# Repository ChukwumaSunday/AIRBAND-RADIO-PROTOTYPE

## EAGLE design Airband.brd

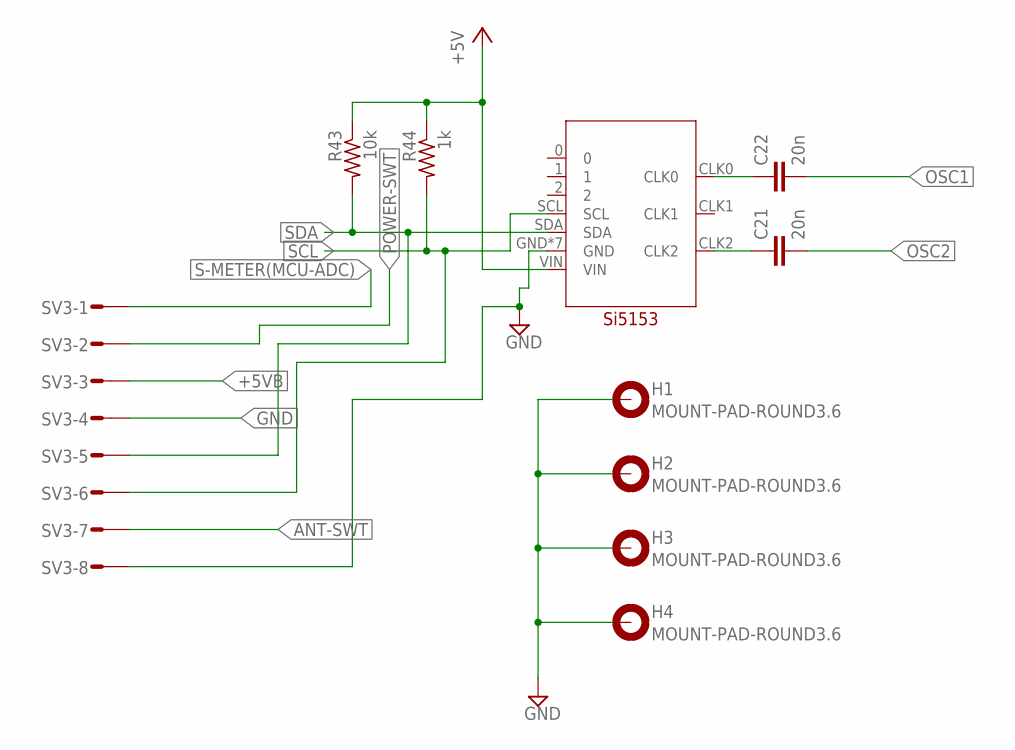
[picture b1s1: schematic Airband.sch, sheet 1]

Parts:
C21, C22: 20n; C0805
H1, H2, H3, H4: MOUNT-PAD-ROUND3.6; 3,6-PAD
R43: 10k; R0805
R44: 1k; R0805
SV3: MT6-8
U$10: DEVELOPMENT-BOARDS$1_SI5153SI5153; DEVELOPMENT-BOARDS$1_SI5153

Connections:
+5VA: R43.1, R44.1, U$10.VIN; also elsewhere on the board
+5VB: SV3.3; also elsewhere on the board
ANT-SWT: SV3.7; also elsewhere on the board
GND: H1.B3,6, H2.B3,6, H3.B3,6, H4.B3,6, SV3.4, SV3.8, U$10.GND, U$10.GND0 (GND), U$10.GND00 (GND), U$10.GND1 (GND), U$10.GND2 (GND), U$10.GND11 (GND), U$10.GND22 (GND); also elsewhere on the board
unnamed: C21.1, U$10.CLK2
unnamed: C22.1, U$10.CLK0
OSC1: C22.2; also elsewhere on the board
OSC2: C21.2; also elsewhere on the board
POWER-SWT: SV3.2; also elsewhere on the board
S-METER(MCU-ADC): SV3.1; also elsewhere on the board
SCL: R44.2, SV3.6, U$10.SCL
SDA: R43.2, SV3.5, U$10.SDA

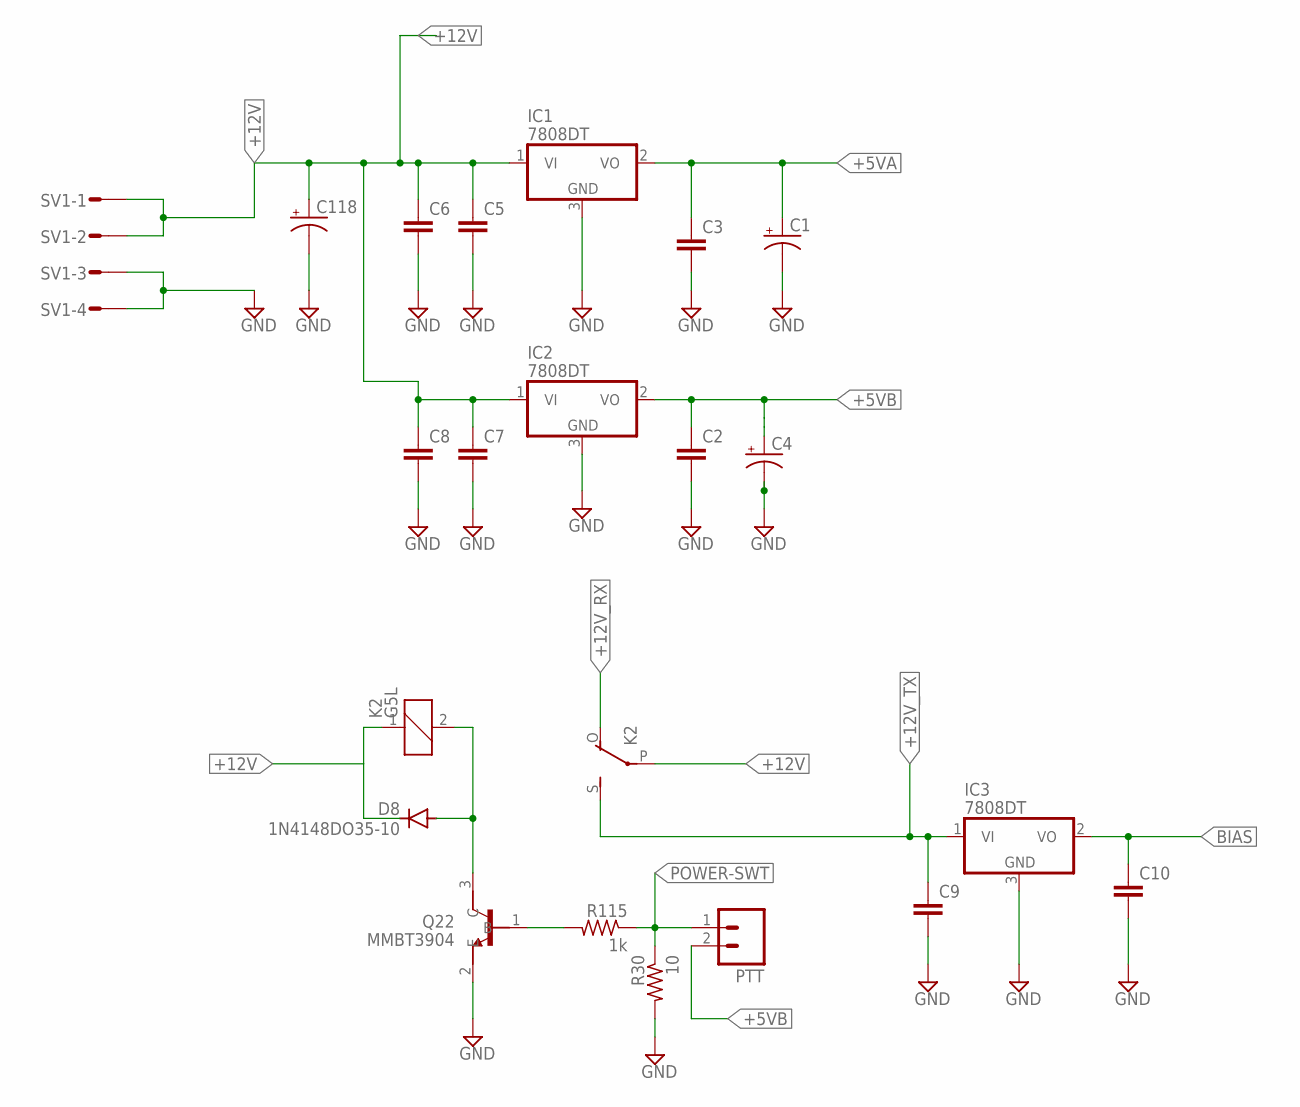
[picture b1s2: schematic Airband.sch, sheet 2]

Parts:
C1, C4, C118: CPOL-US153CLV-0405; 153CLV-0405
C2, C3, C5, C6, C7, C8, C9, C10: C-EUC0805; C0805
D8: 1N4148DO35-10; DO35-7SMD
IC1, IC2, IC3: 7808DT; TO252
K2: G5L; G5LE
PTT: M02; 02P
Q22: MMBT3904; SOT95P240X120-3N
R30: 10; R0805
R115: 1k; R0805
SV1: MT6-4Y

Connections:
+5VA: C1.+, C3.1, IC1.2 (VO); also elsewhere on the board
+5VB: C2.1, C4.+, IC2.2 (VO), PTT.2; also elsewhere on the board
+12V: C5.1, C6.1, C7.1, C8.1, C118.+, D8.C, IC1.1 (VI), IC2.1 (VI), K2.1, K2.P, SV1.1, SV1.2; also elsewhere on the board
+12V_RX: K2.O
+12V_TX: C9.1, IC3.1 (VI), K2.S
BIAS: C10.1, IC3.2 (VO); also elsewhere on the board
GND: C1.-, C2.2, C3.2, C4.-, C5.2, C6.2, C7.2, C8.2, C9.2, C10.2, C118.-, IC1.3 (GND), IC2.3 (GND), IC3.3 (GND), Q22.2 (E), R30.2, SV1.3, SV1.4; also elsewhere on the board
unnamed: D8.A, K2.2, Q22.3 (C)
unnamed: Q22.1 (B), R115.2
POWER-SWT: PTT.1, R30.1, R115.1; also elsewhere on the board

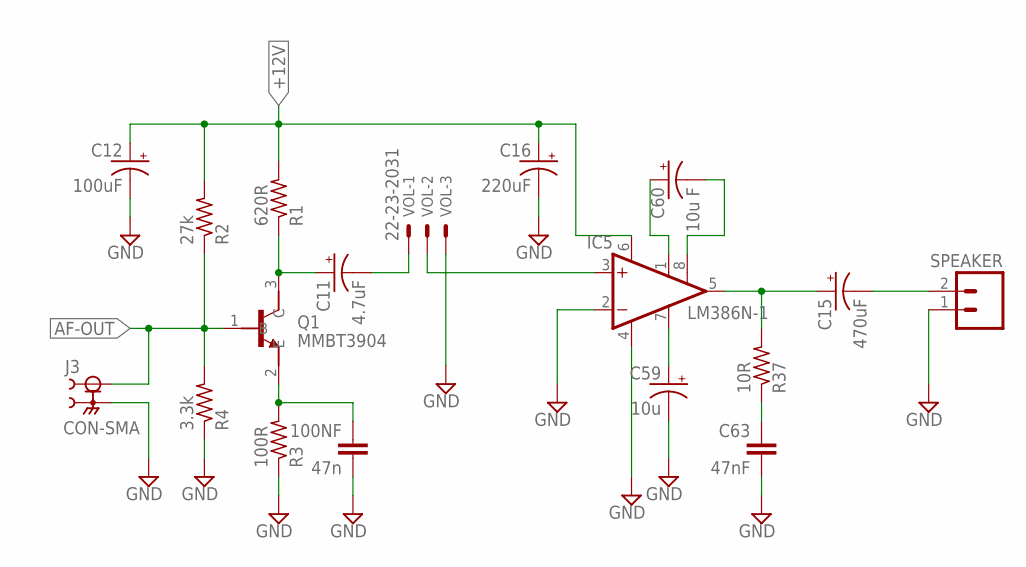
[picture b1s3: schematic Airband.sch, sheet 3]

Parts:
100NF: 47n; C0805
C11: 4.7uF; 153CLV-0405
C12: 100uF; 153CLV-0405
C15: 470uF; 153CLV-0405
C16: 220uF; 153CLV-0405
C59: 10u; 153CLV-0405
C60: 10u F; 153CLV-0405
C63: 47nF; C0805
IC5: LM386N-1; DIL08
J3: CON-SMA; CON-SMA-MINI
Q1: MMBT3904; SOT95P240X120-3N
R1: 620R; R0805
R2: 27k; R0805
R3: 100R; R0805
R4: 3.3k; R0805
R37: 10R; R0805
SPEAKER: M02; 02P
VOL: 22-23-2031

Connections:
+12V: C12.+, C16.+, IC5.6 (VS), R1.2, R2.2; also elsewhere on the board
AF-OUT: J3.1, Q1.1 (B), R2.1, R4.2; also elsewhere on the board
GND: 100NF.2, C12.-, C16.-, C59.-, C63.2, IC5.2 (-IN), IC5.4 (GND), J3.S1 (2), J3.S2 (2), J3.S3 (2), J3.S4 (2), R3.1, R4.1, SPEAKER.1, VOL.3; also elsewhere on the board
unnamed: 100NF.1, Q1.2 (E), R3.2
unnamed: C11.+, Q1.3 (C), R1.1
unnamed: C11.-, VOL.1
unnamed: IC5.3 (+IN), VOL.2
unnamed: C15.+, IC5.5 (OUT), R37.2
unnamed: C15.-, SPEAKER.2
unnamed: C59.+, IC5.7 (BYPASS)
unnamed: C63.1, R37.1
unnamed: C60.+, IC5.1 (GAIN)
unnamed: C60.-, IC5.8 (GAIN)

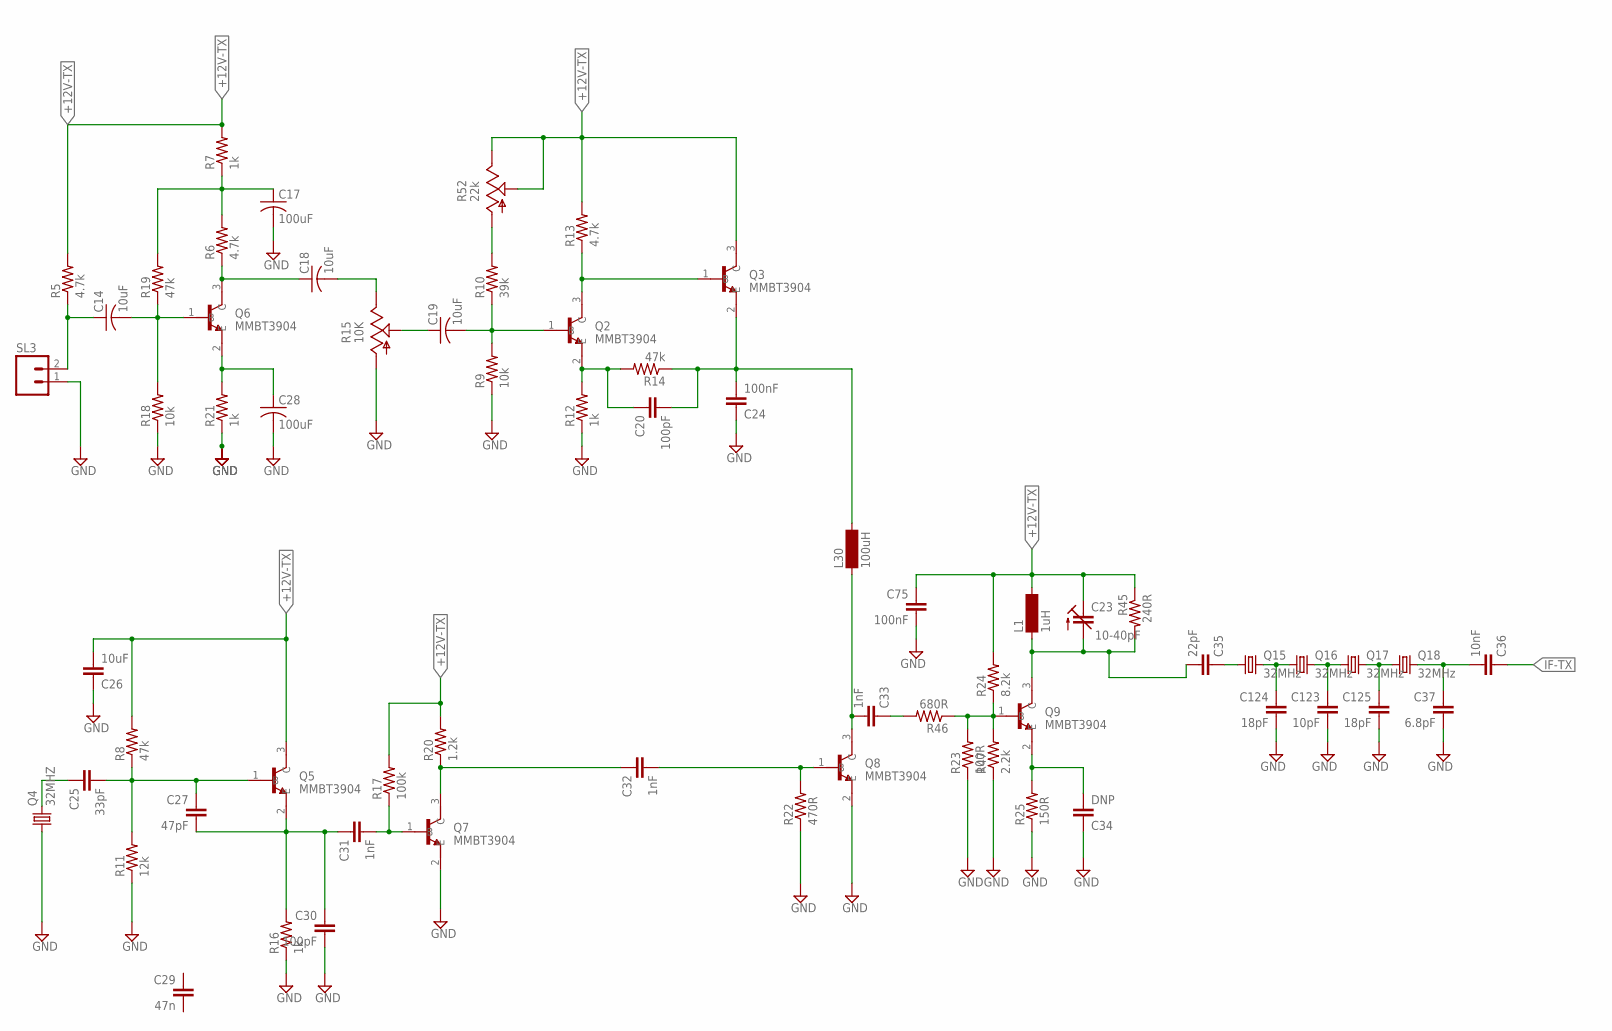
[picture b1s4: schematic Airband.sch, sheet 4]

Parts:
C14, C18, C19: 10uF; C0805K
C17, C28: 100uF; C0805K
C20, C30: 100pF; C0805
C23: 10-40pF; CTRIM3008
C24, C75: 100nF; C0805
C25: 33pF; C0805
C26: 10uF; C0805
C27: 47pF; C0805
C29: 47n; C0805
C31, C32, C33: 1nF; C0805
C34: DNP; C0805
C35: 22pF; C0805
C36: 10nF; C0805
C37: 6.8pF; C0805
C123: 10pF; C0805
C124, C125: 18pF; C0805
L1: 1uH; SM-Z15
L30: 100uH; SM-Z15
Q2, Q3, Q5, Q6, Q7, Q8, Q9: MMBT3904; SOT95P240X120-3N
Q4: 32MHZ; HC49/S
Q15, Q16, Q17, Q18: 32MHz; HC49/S
R5, R6, R13: 4.7k; R0805
R7, R12, R16, R21: 1k; R0805
R8, R14, R19: 47k; R0805
R9, R18: 10k; R0805
R10: 39k; R0805
R11: 12k; R0805
R15: 10K; B64Y
R17: 100k; R0805
R20: 1.2k; R0805
R22: 470R; R0805
R23: 100R; R0805
R24: 8.2k; R0805
R25: 150R; R0805
R45: 240R; R0805
R46: 680R; R0805
R47: 2.2k; R0805
R52: 22k; B64Y
SL3: M02; 02P

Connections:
+12V-TX: C23.+ (E), C26.2, C75.1, L1.2, Q3.3 (C), Q5.3 (C), R5.2, R7.2, R8.2, R13.2, R17.2, R20.2, R24.2, R45.1, R52.E, R52.S; also elsewhere on the board
GND: C17.2, C24.1, C26.1, C28.2, C30.2, C34.1, C37.2, C75.2, C123.2, C124.2, C125.2, Q4.1, Q7.2 (E), Q8.2 (E), R9.1, R11.1, R12.1, R15.A, R16.1, R18.1, R21.1, R22.1, R23.1, R25.1, R47.1, SL3.1; also elsewhere on the board
IF-TX: C36.1; also elsewhere on the board
unnamed: C23.- (A), C35.2, L1.1, Q9.3 (C), R45.2
unnamed: C14.1, R5.1, SL3.2
unnamed: C17.1, R6.2, R7.1, R19.2
unnamed: C18.1, Q6.3 (C), R6.1
unnamed: C14.2, Q6.1 (B), R18.2, R19.1
unnamed: C20.1, Q2.2 (E), R12.2, R14.2
unnamed: C28.1, Q6.2 (E), R21.2
unnamed: C19.2, Q2.1 (B), R9.2, R10.1
unnamed: Q2.3 (C), Q3.1 (B), R13.1
unnamed: C20.2, C24.2, L30.2, Q3.2 (E), R14.1
unnamed: R10.2, R52.A
unnamed: C33.1, R46.2
unnamed: C35.1, Q15.1
unnamed: C25.2, C27.1, Q5.1 (B), R8.1, R11.2
unnamed: C19.1, R15.S
unnamed: C18.2, R15.E
unnamed: C32.2, Q8.1 (B), R22.2
unnamed: C27.2, C30.1, C31.1, Q5.2 (E), R16.2
unnamed: C25.1, Q4.2
unnamed: C31.2, Q7.1 (B), R17.1
unnamed: C32.1, Q7.3 (C), R20.1
unnamed: C33.2, L30.1, Q8.3 (C)
unnamed: Q9.1 (B), R23.2, R24.1, R46.1, R47.2
unnamed: C34.2, Q9.2 (E), R25.2
unnamed: C36.2, C37.1, Q18.2
unnamed: C124.1, Q15.2, Q16.1
unnamed: C123.1, Q16.2, Q17.1
unnamed: C125.1, Q17.2, Q18.1

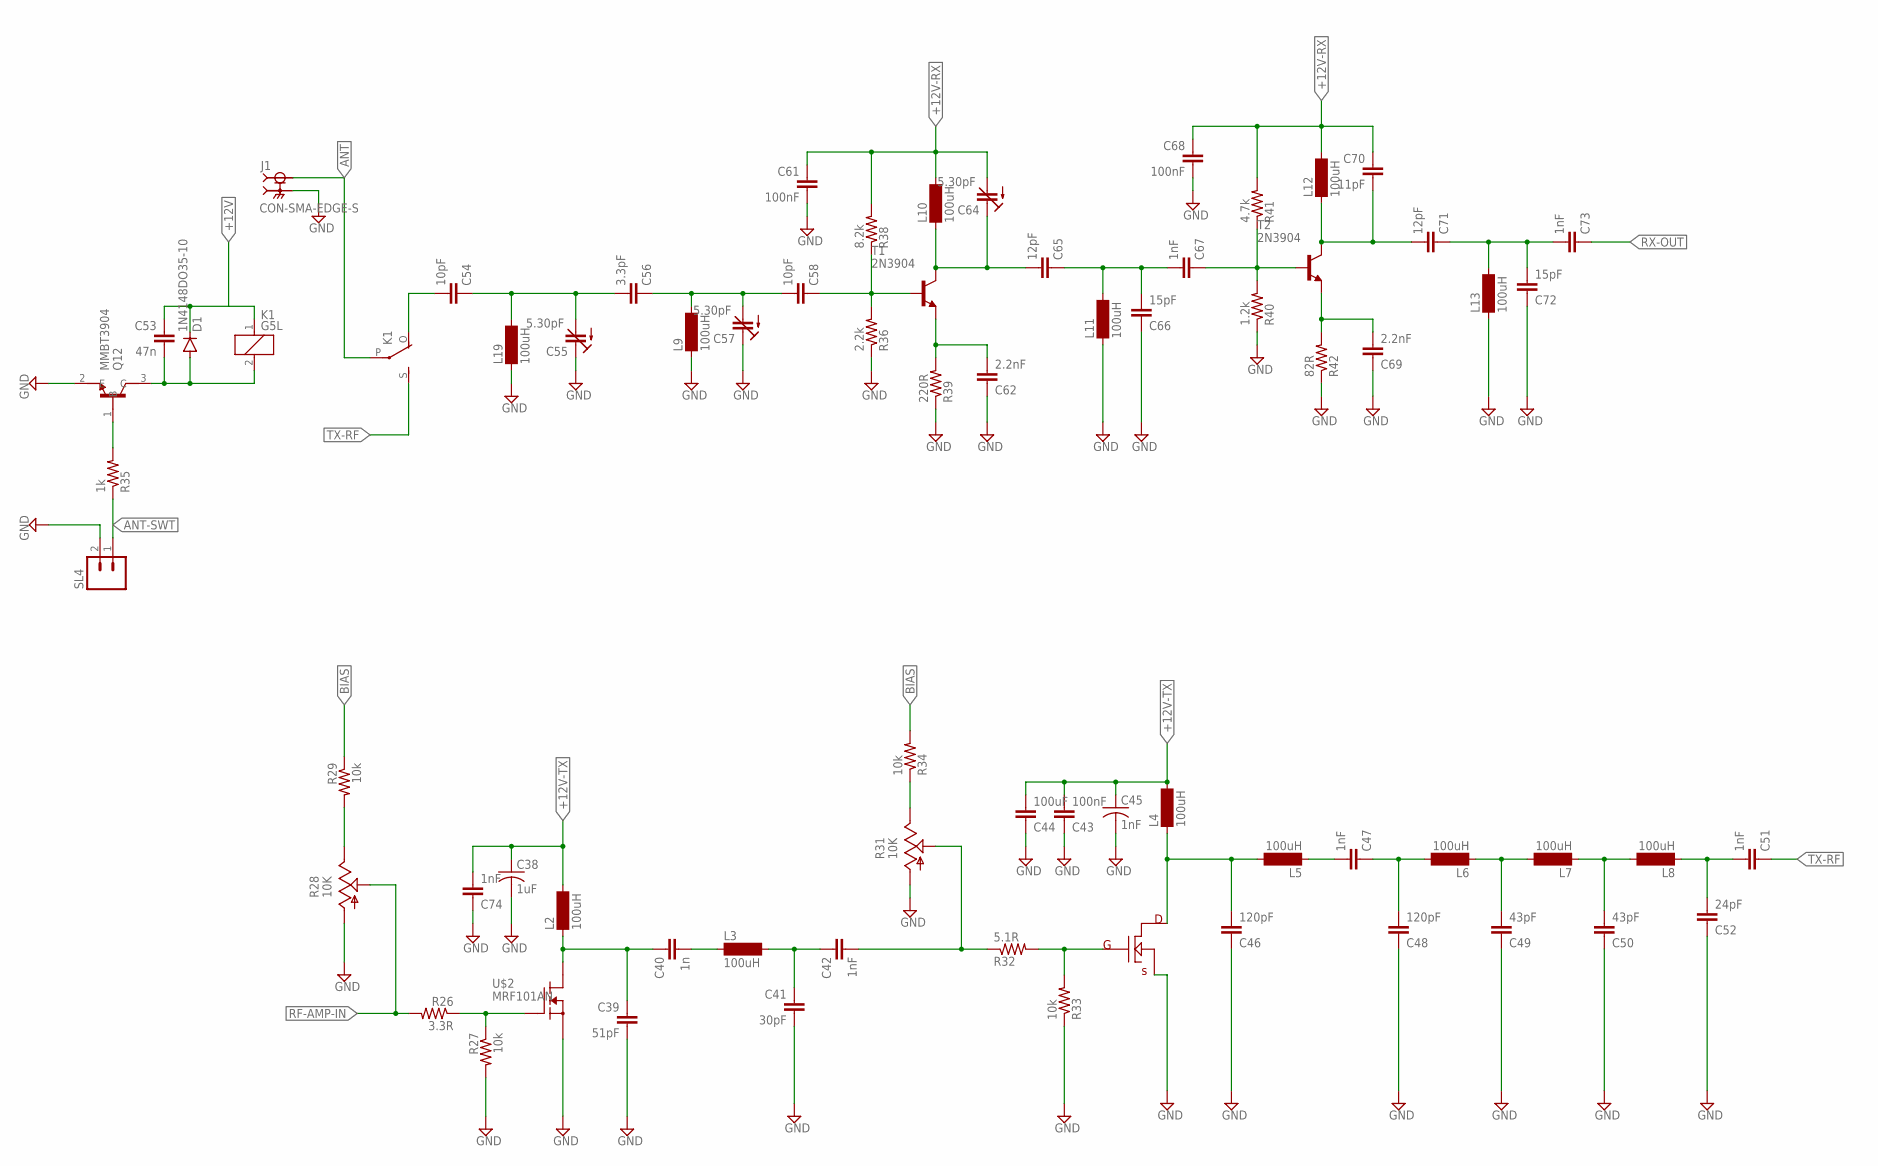
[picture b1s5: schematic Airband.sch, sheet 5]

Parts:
C38: 1uF; C0805K
C39: 51pF; C0805
C40: 1n; C0805
C41: 30pF; C0805
C42, C47, C51, C67, C73, C74: 1nF; C0805
C43, C61, C68: 100nF; C0805
C44: 100uF; C0805
C45: 1nF; C0805K
C46, C48: 120pF; C0805
C49, C50: 43pF; C0805
C52: 24pF; C0805
C53: 47n; C0805
C54, C58: 10pF; C0805
C55, C57, C64: 5.30pF; CTRIM3008
C56: 3.3pF; C0805
C62, C69: 2.2nF; C0805
C65, C71: 12pF; C0805
C66, C72: 15pF; C0805
C70: 11pF; C0805
D1: 1N4148DO35-10; DO35-7SMD
J1: CON-SMA-EDGE-S; RFSOLUTIONS_CON-SMA-EDGE-S
K1: G5L; G5LE
L2, L3, L4, L5, L6, L7, L8, L9, L10, L11, L12, L13, L19: 100uH; SM-Z15
Q12: MMBT3904; SOT95P240X120-3N
R26: 3.3R; R0805
R27, R29, R33, R34: 10k; R0805
R28, R31: 10K; B64Y
R32: 5.1R; R0805
R35: 1k; R0805
R36: 2.2k; R0805
R38: 8.2k; R0805
R39: 220R; R0805
R40: 1.2k; R0805
R41: 4.7k; R0805
R42: 82R; R0805
SL4: M02; 02P
T1, T2: 2N3904; TO92-EBC(SMD)
U$1: RD04HMS2; RD07MUS2B
U$2: MRF101AN; TO220

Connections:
+12V: C53.1, D1.C, K1.1; also elsewhere on the board
+12V-RX: C61.1, C64.- (A), C68.1, C70.1, L10.2, L12.2, R38.2, R41.2; also elsewhere on the board
+12V-TX: C38.1, C43.2, C44.2, C45.1, C74.2, L2.2, L4.2; also elsewhere on the board
ANT: J1.1, K1.P
ANT-SWT: R35.1, SL4.1; also elsewhere on the board
BIAS: R29.1, R34.2; also elsewhere on the board
GND: C38.2, C39.2, C41.2, C43.1, C44.1, C45.2, C46.1, C48.1, C49.1, C50.1, C52.1, C55.+ (E), C57.+ (E), C61.2, C62.1, C66.1, C68.2, C69.1, C72.1, C74.1, J1.G1 (2), J1.G2 (2), J1.G3 (2), J1.G4 (2), L9.1, L11.1, L13.1, L19.1, Q12.2 (E), R27.2, R28.A, R31.A, R33.1, R36.1, R39.1, R40.1, R42.1, SL4.2, U$1.S, U$2.2 (S); also elsewhere on the board
unnamed: R28.E, R29.2
unnamed: R26.1, R27.1, U$2.1 (G)
unnamed: C39.1, C40.1, L2.1, U$2.3 (D)
unnamed: C53.2, D1.A, K1.2, Q12.3 (C)
unnamed: C40.2, L3.1
unnamed: C41.1, C42.1, L3.2
unnamed: C42.2, R31.S, R32.1
unnamed: R32.2, R33.2, U$1.G
unnamed: C46.2, L4.1, L5.2, U$1.D
unnamed: Q12.1 (B), R35.2
unnamed: R31.E, R34.1
unnamed: C54.2, K1.O
unnamed: C47.2, L5.1
unnamed: C47.1, C48.2, L6.2
unnamed: C49.2, L6.1, L7.2
unnamed: C50.2, L7.1, L8.2
unnamed: C51.2, C52.2, L8.1
unnamed: C54.1, C55.- (A), C56.2, L19.2
unnamed: C56.1, C57.- (A), C58.2, L9.2
unnamed: C58.1, R36.2, R38.1, T1.B
unnamed: C62.2, R39.2, T1.E
unnamed: C64.+ (E), C65.2, L10.1, T1.C
unnamed: C67.1, R40.2, R41.1, T2.B
unnamed: C65.1, C66.2, C67.2, L11.2
unnamed: C69.2, R42.2, T2.E
unnamed: C70.2, C71.2, L12.1, T2.C
unnamed: C71.1, C72.2, C73.2, L13.2
RF-AMP-IN: R26.2, R28.S; also elsewhere on the board
RX-OUT: C73.1; also elsewhere on the board
TX-RF: C51.1, K1.S

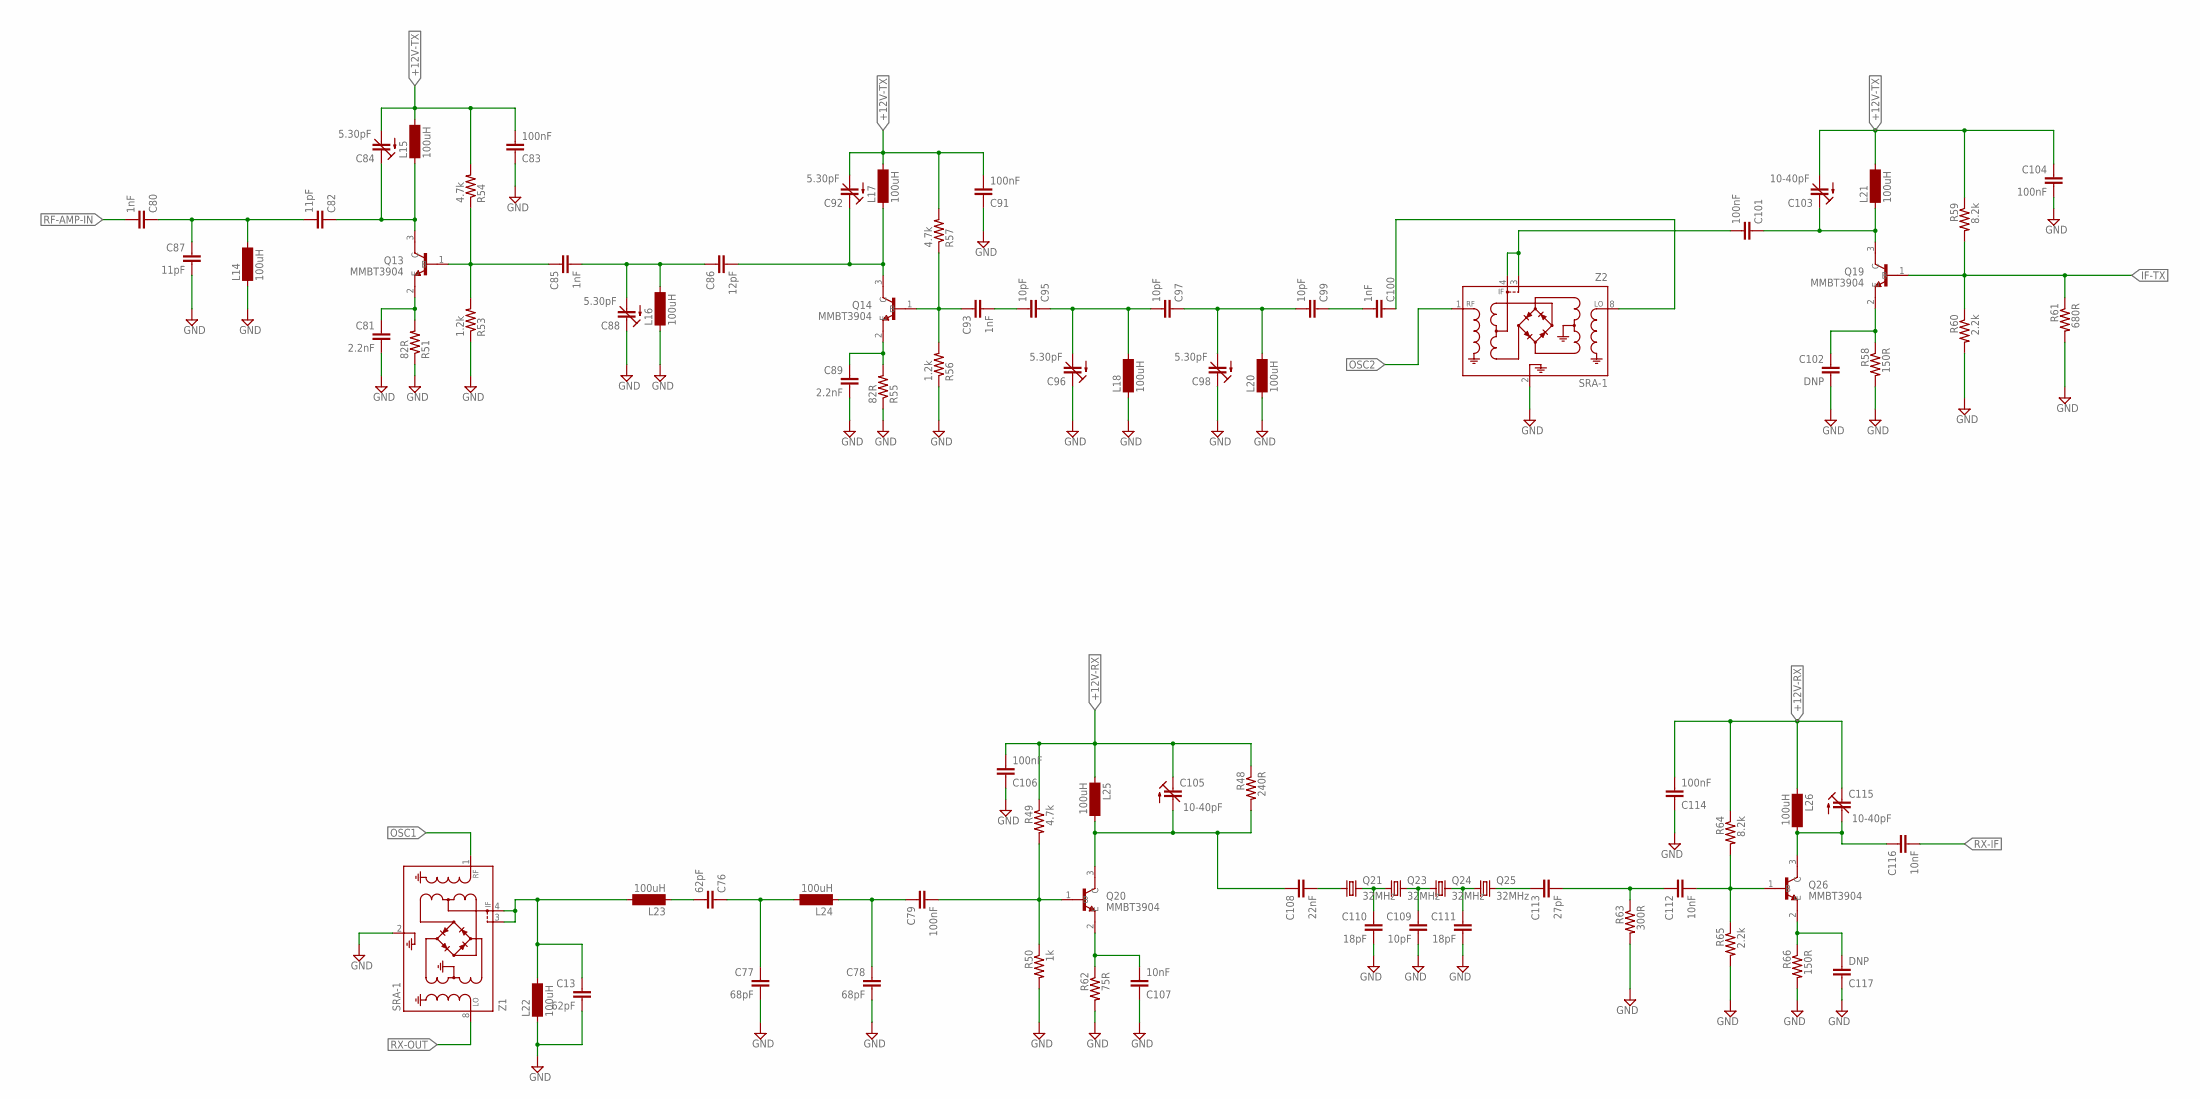
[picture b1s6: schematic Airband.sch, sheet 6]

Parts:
C13, C76: 62pF; C0805
C77, C78: 68pF; C0805
C79, C83, C91, C101, C104, C106, C114: 100nF; C0805
C80, C85, C93, C100: 1nF; C0805
C81, C89: 2.2nF; C0805
C82, C87: 11pF; C0805
C84, C88, C92, C96, C98: 5.30pF; CTRIM3008
C86: 12pF; C0805
C95, C97, C99, C109: 10pF; C0805
C102, C117: DNP; C0805
C103, C105, C115: 10-40pF; CTRIM3008
C107, C112, C116: 10nF; C0805
C108: 22nF; C0805
C110, C111: 18pF; C0805
C113: 27pF; C0805
L14, L15, L16, L17, L18, L20, L21, L22, L23, L24, L25, L26: 100uH; SM-Z15
Q13, Q14, Q19, Q20, Q26: MMBT3904; SOT95P240X120-3N
Q21, Q23, Q24, Q25: 32MHz; HC49/S
R48: 240R; R0805
R49, R54, R57: 4.7k; R0805
R50: 1k; R0805
R51, R55: 82R; R0805
R53, R56: 1.2k; R0805
R58, R66: 150R; R0805
R59, R64: 8.2k; R0805
R60, R65: 2.2k; R0805
R61: 680R; R0805
R62: 75R; R0805
R63: 300R; R0805
Z1, Z2: SRA-1; A01

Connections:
+12V-RX: C105.+ (E), C106.2, C114.2, C115.+ (E), L25.1, L26.1, R48.1, R49.1, R64.1; also elsewhere on the board
+12V-TX: C83.2, C84.- (A), C91.2, C92.- (A), C103.- (A), C104.1, L15.2, L17.2, L21.2, R54.2, R57.2, R59.1; also elsewhere on the board
GND: C13.2, C77.2, C78.2, C81.2, C83.1, C87.2, C88.+ (E), C89.2, C91.1, C96.+ (E), C98.+ (E), C102.2, C104.2, C106.1, C107.1, C109.2, C110.2, C111.2, C114.1, C117.1, L14.1, L16.1, L18.1, L20.1, L22.1, R50.2, R51.1, R53.1, R55.1, R56.1, R58.2, R60.2, R61.2, R62.2, R63.2, R65.2, R66.2, Z1.2 (CASEGROUND), Z1.5 (GND), Z1.6 (GND), Z1.7 (GND), Z2.2 (CASEGROUND), Z2.5 (GND), Z2.6 (GND), Z2.7 (GND); also elsewhere on the board
IF-TX: Q19.1 (B), R59.2, R60.1, R61.1; also elsewhere on the board
unnamed: C76.2, L23.1
unnamed: C76.1, C77.1, L24.2
unnamed: C78.1, C79.1, L24.1
unnamed: C100.1, Z2.8 (L)
unnamed: C82.1, C84.+ (E), L15.1, Q13.3 (C)
unnamed: C85.1, Q13.1 (B), R53.2, R54.1
unnamed: C85.2, C86.1, C88.- (A), L16.2
unnamed: C80.1, C82.2, C87.1, L14.2
unnamed: C81.1, Q13.2 (E), R51.2
unnamed: C86.2, C92.+ (E), L17.1, Q14.3 (C)
unnamed: C93.1, Q14.1 (B), R56.2, R57.1
unnamed: C93.2, C95.2
unnamed: C89.1, Q14.2 (E), R55.2
unnamed: C95.1, C96.- (A), C97.2, L18.2
unnamed: C97.1, C98.- (A), C99.2, L20.2
unnamed: C99.1, C100.2
unnamed: C101.1, C103.+ (E), L21.1, Q19.3 (C)
unnamed: C102.1, Q19.2 (E), R58.1
unnamed: C79.2, Q20.1 (B), R49.2, R50.1
unnamed: C107.2, Q20.2 (E), R62.1
unnamed: C105.- (A), C108.1, L25.2, Q20.3 (C), R48.2
unnamed: C110.1, Q21.2, Q23.1
unnamed: C109.1, Q23.2, Q24.1
unnamed: C111.1, Q24.2, Q25.1
unnamed: C108.2, Q21.1
unnamed: C112.1, C113.2, R63.1
unnamed: C113.1, Q25.2
unnamed: C112.2, Q26.1 (B), R64.2, R65.1
unnamed: C117.2, Q26.2 (E), R66.1
unnamed: C115.- (A), C116.1, L26.2, Q26.3 (C)
unnamed: C101.2, Z2.3 (IF), Z2.4 (IF)
unnamed: C13.1, L22.2, L23.2, Z1.3 (IF), Z1.4 (IF)
OSC1: Z1.1 (R); also elsewhere on the board
OSC2: Z2.1 (R); also elsewhere on the board
RF-AMP-IN: C80.2; also elsewhere on the board
RX-IF: C116.2; also elsewhere on the board
RX-OUT: Z1.8 (L); also elsewhere on the board

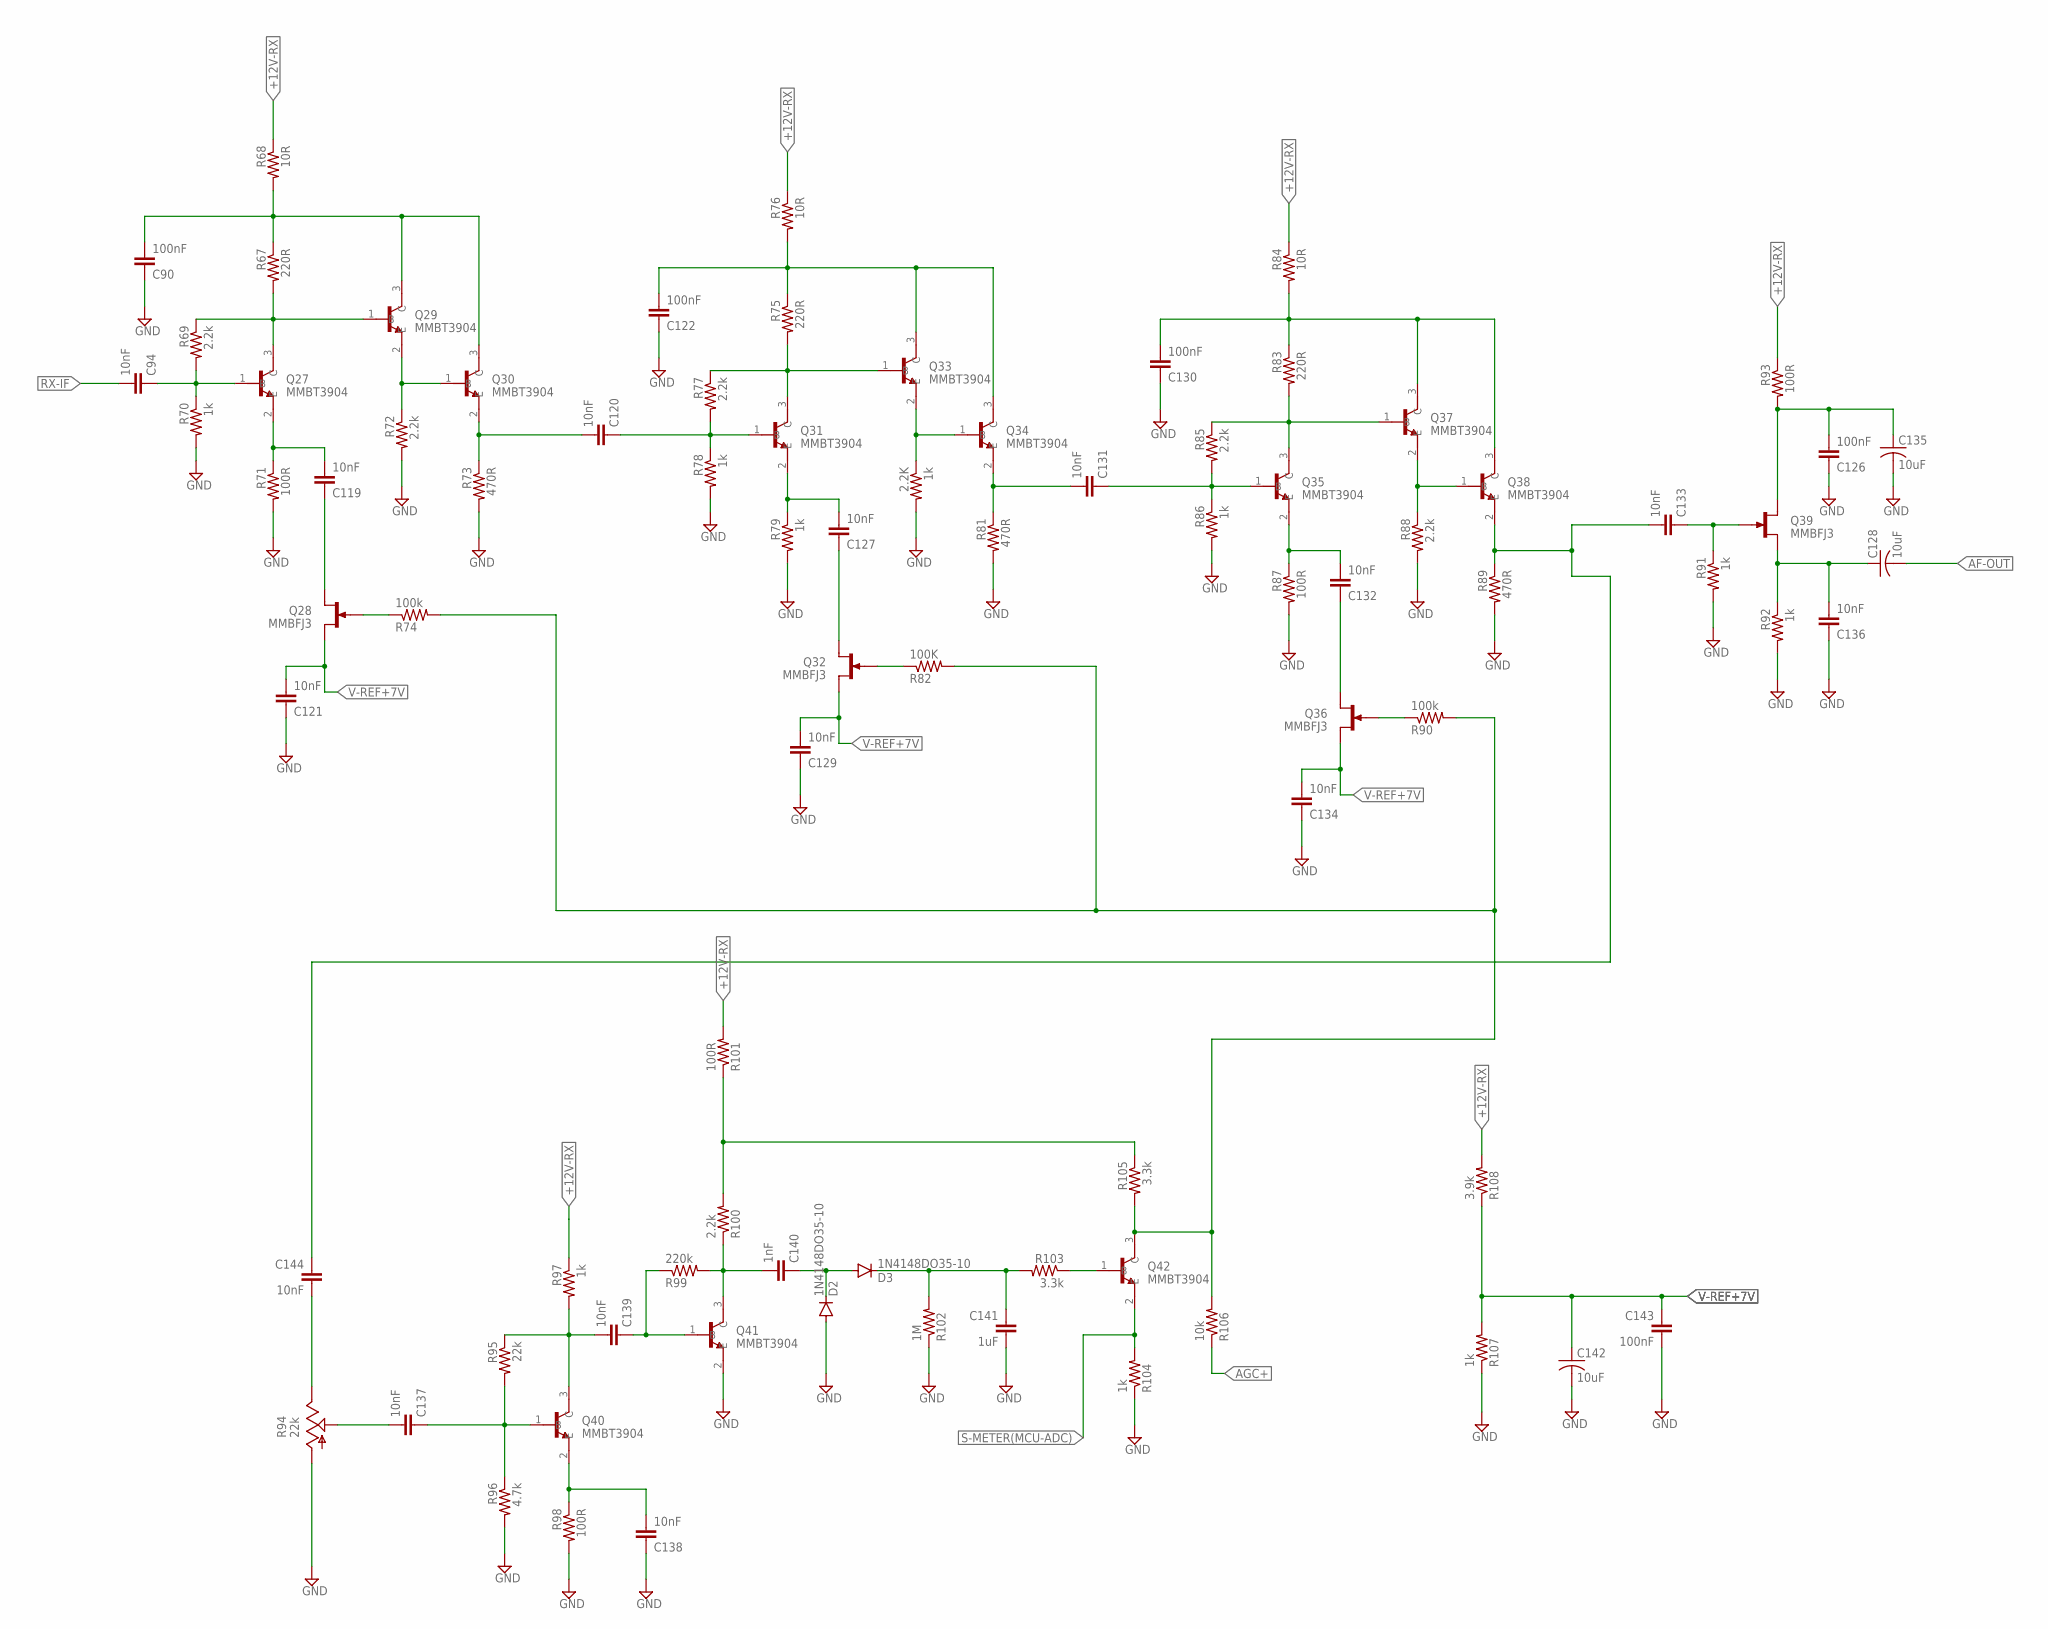
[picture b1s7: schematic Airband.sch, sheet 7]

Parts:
2.2K: 1k; R0805
C90, C122, C126, C130, C143: 100nF; C0805
C94, C119, C120, C121, C127, C129, C131, C132, C133, C134, C136, C137, C138, C139, C144: 10nF; C0805
C128, C135, C142: 10uF; C0805K
C140: 1nF; C0805
C141: 1uF; C0805
D2, D3: 1N4148DO35-10; DO35-7SMD
Q27, Q29, Q30, Q31, Q33, Q34, Q35, Q37, Q38, Q40, Q41, Q42: MMBT3904; SOT95P240X120-3N
Q28, Q32, Q36, Q39: MMBFJ3; SOT23
R67, R75, R83: 220R; R0805
R68, R76, R84: 10R; R0805
R69, R72, R77, R85, R88, R100: 2.2k; R0805
R70, R78, R79, R86, R91, R92, R97, R104, R107: 1k; R0805
R71, R87, R93, R98, R101: 100R; R0805
R73, R81, R89: 470R; R0805
R74, R90: 100k; R0805
R82: 100K; R0805
R94: 22k; B64Y
R95: 22k; R0805
R96: 4.7k; R0805
R99: 220k; R0805
R102: 1M; R0805
R103, R105: 3.3k; R0805
R106: 10k; R0805
R108: 3.9k; R0805

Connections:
+12V-RX: R68.1, R76.1, R84.1, R93.1, R97.1, R101.2, R108.2; also elsewhere on the board
AF-OUT: C128.2; also elsewhere on the board
AGC+: R106.1
GND: 2.2K.2, C90.1, C121.1, C122.1, C126.1, C129.1, C130.1, C134.1, C135.2, C136.1, C138.1, C141.2, C142.2, C143.2, D2.A, Q41.2 (E), R70.2, R71.2, R72.2, R73.2, R78.2, R79.2, R81.2, R86.2, R87.2, R88.2, R89.2, R91.2, R92.2, R94.A, R96.2, R98.2, R102.1, R104.1, R107.1; also elsewhere on the board
unnamed: C94.1, Q27.1 (B), R69.2, R70.1
unnamed: C119.2, Q27.2 (E), R71.1
unnamed: C119.1, Q28.1 (D)
unnamed: Q28.3 (G), R74.1
unnamed: Q27.3 (C), Q29.1 (B), R67.2, R69.1
unnamed: C90.2, Q29.3 (C), Q30.3 (C), R67.1, R68.2
unnamed: Q29.2 (E), Q30.1 (B), R72.1
unnamed: C120.2, Q30.2 (E), R73.1
unnamed: C120.1, Q31.1 (B), R77.2, R78.1
unnamed: C127.2, Q31.2 (E), R79.1
unnamed: C127.1, Q32.1 (D)
unnamed: Q32.3 (G), R82.1
unnamed: Q31.3 (C), Q33.1 (B), R75.2, R77.1
unnamed: C122.2, Q33.3 (C), Q34.3 (C), R75.1, R76.2
unnamed: 2.2K.1, Q33.2 (E), Q34.1 (B)
unnamed: C131.2, Q34.2 (E), R81.1
unnamed: C131.1, Q35.1 (B), R85.2, R86.1
unnamed: C132.2, Q35.2 (E), R87.1
unnamed: C132.1, Q36.1 (D)
unnamed: Q36.3 (G), R90.1
unnamed: Q35.3 (C), Q37.1 (B), R83.2, R85.1
unnamed: C130.2, Q37.3 (C), Q38.3 (C), R83.1, R84.2
unnamed: Q37.2 (E), Q38.1 (B), R88.1
unnamed: C133.2, C144.1, Q38.2 (E), R89.1
unnamed: Q42.3 (C), R74.2, R82.2, R90.2, R105.2, R106.2
unnamed: C128.1, C136.2, Q39.2 (S), R92.1
unnamed: C133.1, Q39.3 (G), R91.1
unnamed: C126.2, C135.1, Q39.1 (D), R93.2
unnamed: C144.2, R94.E
unnamed: Q42.1 (B), R103.1
unnamed: C141.1, D3.C, R102.2, R103.2
unnamed: C140.1, D2.C, D3.A
unnamed: C140.2, Q41.3 (C), R99.2, R100.1
unnamed: C139.1, Q41.1 (B), R99.1
unnamed: C139.2, Q40.3 (C), R95.1, R97.2
unnamed: C137.2, R94.S
unnamed: C137.1, Q40.1 (B), R95.2, R96.1
unnamed: C138.2, Q40.2 (E), R98.1
unnamed: R100.2, R101.1, R105.1
RX-IF: C94.2; also elsewhere on the board
S-METER(MCU-ADC): Q42.2 (E), R104.2; also elsewhere on the board
V-REF+7V: C121.2, C129.2, C134.2, C142.1, C143.1, Q28.2 (S), Q32.2 (S), Q36.2 (S), R107.2, R108.1

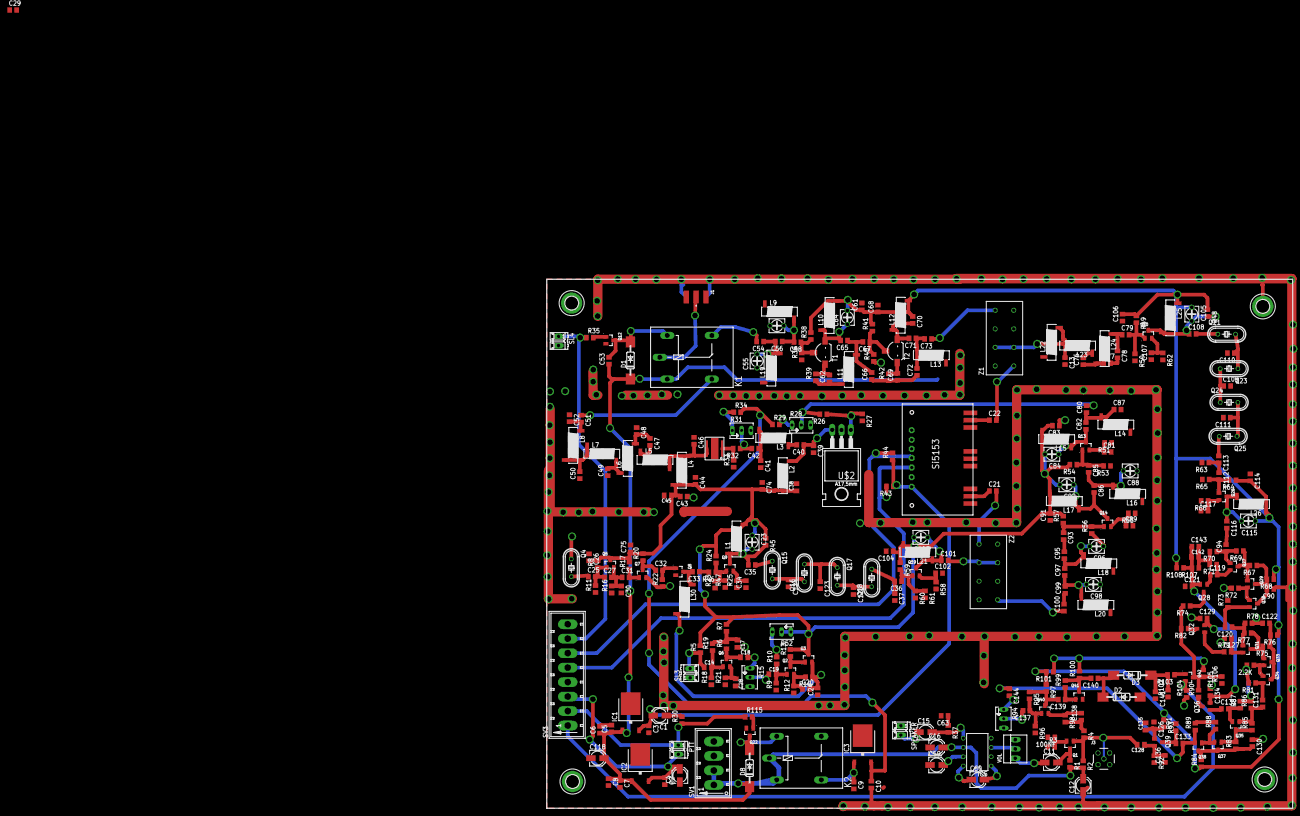
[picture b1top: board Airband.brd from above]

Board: 2 copper layers, 204.1 x 144.8 mm, 351 parts (0 on the bottom side), 163 nets.
